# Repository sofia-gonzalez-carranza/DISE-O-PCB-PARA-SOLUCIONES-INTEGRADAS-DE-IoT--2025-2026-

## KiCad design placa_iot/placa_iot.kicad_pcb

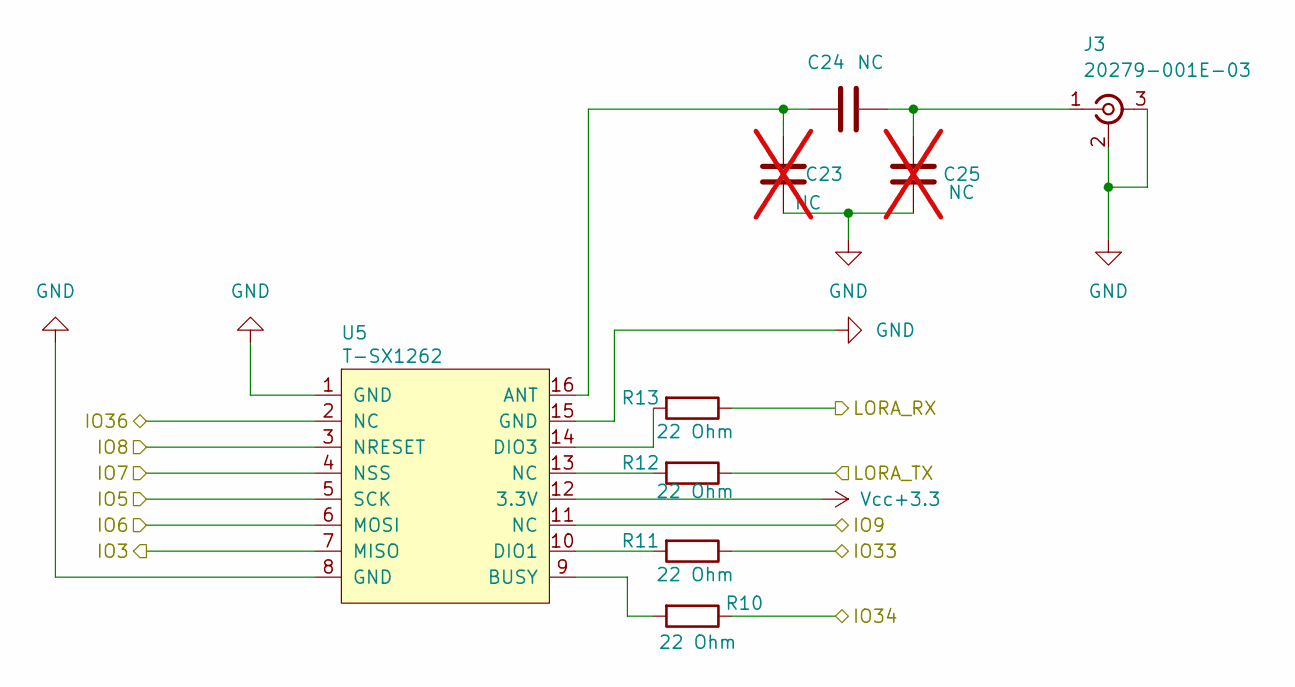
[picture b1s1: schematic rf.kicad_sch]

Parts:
C23, C25: NC; C_0402_1005Metric; not fitted
C24: NC; C_0402_1005Metric
J3: 20279-001E-03; IPEX_MHF_I
R10, R11, R12, R13: 22 Ohm; R_0402_1005Metric
U5: T-SX1262; MODULE_T_SX1262

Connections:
/MICROCONTROLADOR/IO3: U5.7 (MISO); also elsewhere on the board
/MICROCONTROLADOR/IO5: U5.5 (SCK); also elsewhere on the board
/MICROCONTROLADOR/IO6: U5.6 (MOSI); also elsewhere on the board
/MICROCONTROLADOR/IO7: U5.4 (NSS); also elsewhere on the board
/MICROCONTROLADOR/IO8: U5.3 (NRESET); also elsewhere on the board
/MICROCONTROLADOR/IO9: U5.11 (NC); also elsewhere on the board
/MICROCONTROLADOR/IO33: R11.1; also elsewhere on the board
/MICROCONTROLADOR/IO34: R10.1; also elsewhere on the board
/MICROCONTROLADOR/IO36: U5.2 (NC); also elsewhere on the board
/MICROCONTROLADOR/LORA_RX: R13.1; also elsewhere on the board
/MICROCONTROLADOR/LORA_TX: R12.1; also elsewhere on the board
GND: C23.2, C25.2, J3.2 (Ext), J3.3 (Ext), U5.1 (GND), U5.8 (GND), U5.15 (GND); also elsewhere on the board
unnamed: C24.2, C25.1, J3.1 (In)
unnamed: R12.2, U5.13 (NC)
unnamed: C23.1, C24.1, U5.16 (ANT)
unnamed: R10.2, U5.9 (BUSY)
unnamed: R11.2, U5.10 (DIO1)
unnamed: R13.2, U5.14 (DIO3)
Vcc+3.3: U5.12 (3.3V); also elsewhere on the board

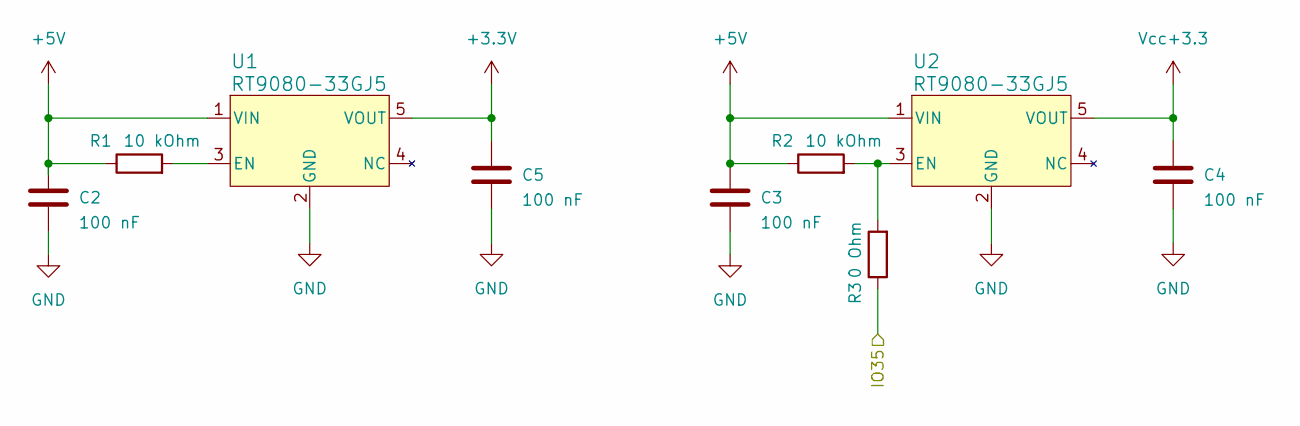
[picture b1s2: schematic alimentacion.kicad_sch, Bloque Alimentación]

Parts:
C2, C3, C4, C5: 100 nF; C_0402_1005Metric
R1, R2: 10 kOhm; R_0402_1005Metric
R3: 0 Ohm; R_0402_1005Metric
U1, U2: RT9080-33GJ5; TSOT-23-5_RIT

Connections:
+3.3V: C5.1, U1.5 (VOUT); also elsewhere on the board
+5V: C2.1, C3.1, R1.1, R2.1, U1.1 (VIN), U2.1 (VIN); also elsewhere on the board
/MICROCONTROLADOR/IO35: R3.1; also elsewhere on the board
GND: C2.2, C3.2, C4.2, C5.2, U1.2 (GND), U2.2 (GND); also elsewhere on the board
unnamed: R1.2, U1.3 (EN)
unnamed: R2.2, R3.2, U2.3 (EN)
Vcc+3.3: C4.1, U2.5 (VOUT); also elsewhere on the board

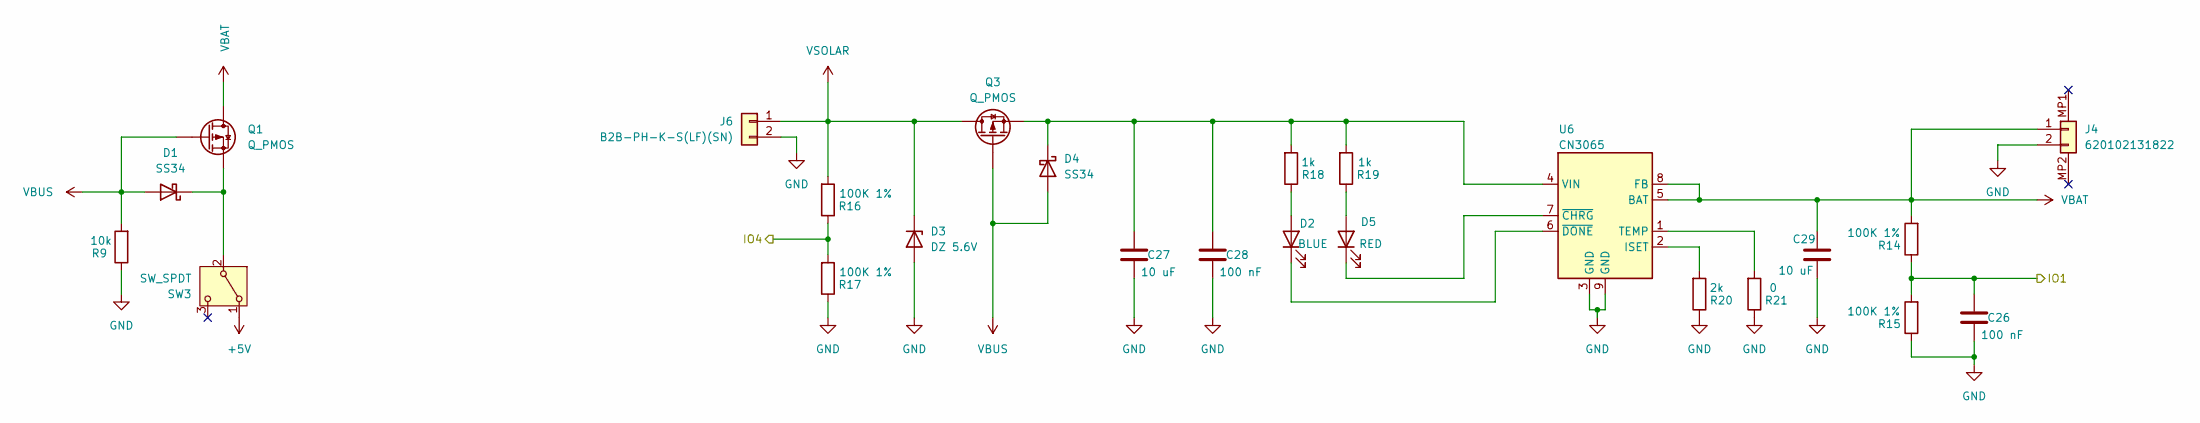
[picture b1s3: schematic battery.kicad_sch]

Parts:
C26, C28: 100 nF; C_0402_1005Metric
C27, C29: 10 uF; C_0402_1005Metric
D1, D4: SS34; D_SMA
D2: BLUE; LED_0402_1005Metric
D3: DZ 5.6V; D_SOD-123
D5: RED; LED_0402_1005Metric
J4: 620102131822; CONN_SMT_MH_SH_P2.00MM_P2
J6: B2B-PH-K-S(LF)(SN); CONN_THT_MV_JST_P2.00MM_P2
Q1, Q3: Q_PMOS; SOT-23
R9: 10k; R_0402_1005Metric
R14, R15, R16, R17: 100K 1%; R_0402_1005Metric
R18, R19: 1k; R_0402_1005Metric
R20: 2k; R_0402_1005Metric
R21: 0; R_0402_1005Metric
SW3: SW_SPDT; SW_Slide_SPDT_Angled_CK_OS102011MA1Q
U6: CN3065; DFN-8-1EP_3x3mm_P0.5mm_EP1.66x2.38mm

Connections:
+5V: SW3.1 (A); also elsewhere on the board
/MICROCONTROLADOR/IO1: C26.1, R14.1, R15.2; also elsewhere on the board
/MICROCONTROLADOR/IO4: R16.1, R17.2; also elsewhere on the board
GND: C26.2, C27.2, C28.2, C29.2, D3.2 (A), J4.2, J6.2, R9.1, R15.1, R17.1, R20.1, R21.1, U6.3 (GND), U6.9 (GND); also elsewhere on the board
unnamed: D1.1 (K), Q1.2 (S), SW3.2 (B)
unnamed: D2.2 (A), R18.1
unnamed: D2.1 (K), U6.6 (~DONE)
unnamed: C27.1, C28.1, D4.1 (K), Q3.2 (S), R18.2, R19.2, U6.4 (VIN)
unnamed: D5.2 (A), R19.1
unnamed: D5.1 (K), U6.7 (~CHRG)
unnamed: R20.2, U6.2 (ISET)
unnamed: R21.2, U6.1 (TEMP)
VBAT: C29.1, J4.1, Q1.3 (D), R14.2, U6.5 (BAT), U6.8 (FB); also elsewhere on the board
VBUS: D1.2 (A), D4.2 (A), Q1.1 (G), Q3.1 (G), R9.2; also elsewhere on the board
VSOLAR: D3.1 (K), J6.1, Q3.3 (D), R16.2

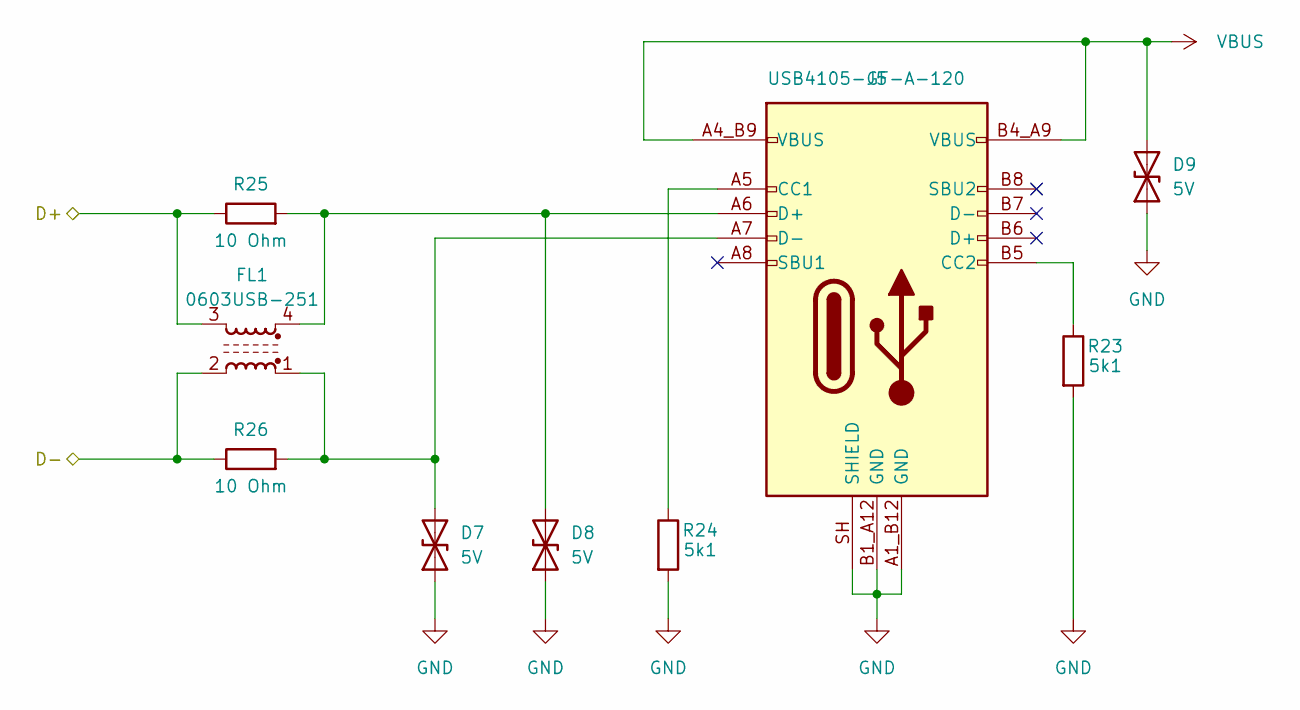
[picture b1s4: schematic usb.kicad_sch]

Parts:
D7, D8, D9: 5V; D_SOD-882
FL1: 0603USB-251; L_CommonModeChoke_Coilcraft_0603USB
J5: USB4105-GF-A-120; CONN_SMT_RH_USBC_P0.50MM_P16
R23, R24: 5k1; R_0402_1005Metric
R25, R26: 10 Ohm; R_0402_1005Metric

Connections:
/MICROCONTROLADOR/DM: FL1.3, R25.1; also elsewhere on the board
/MICROCONTROLADOR/DP: FL1.2, R26.1; also elsewhere on the board
GND: D7.1 (A1), D8.1 (A1), D9.1 (A1), J5.A1_B12 (GND), J5.B1_A12 (GND), J5.SH (SHIELD), R23.2, R24.2; also elsewhere on the board
unnamed: D7.2 (A2), FL1.1, J5.A7 (D-), R26.2
unnamed: D8.2 (A2), FL1.4, J5.A6 (D+), R25.2
unnamed: J5.A5 (CC1), R24.1
unnamed: J5.B5 (CC2), R23.1
VBUS: D9.2 (A2), J5.A4_B9 (VBUS), J5.B4_A9 (VBUS); also elsewhere on the board

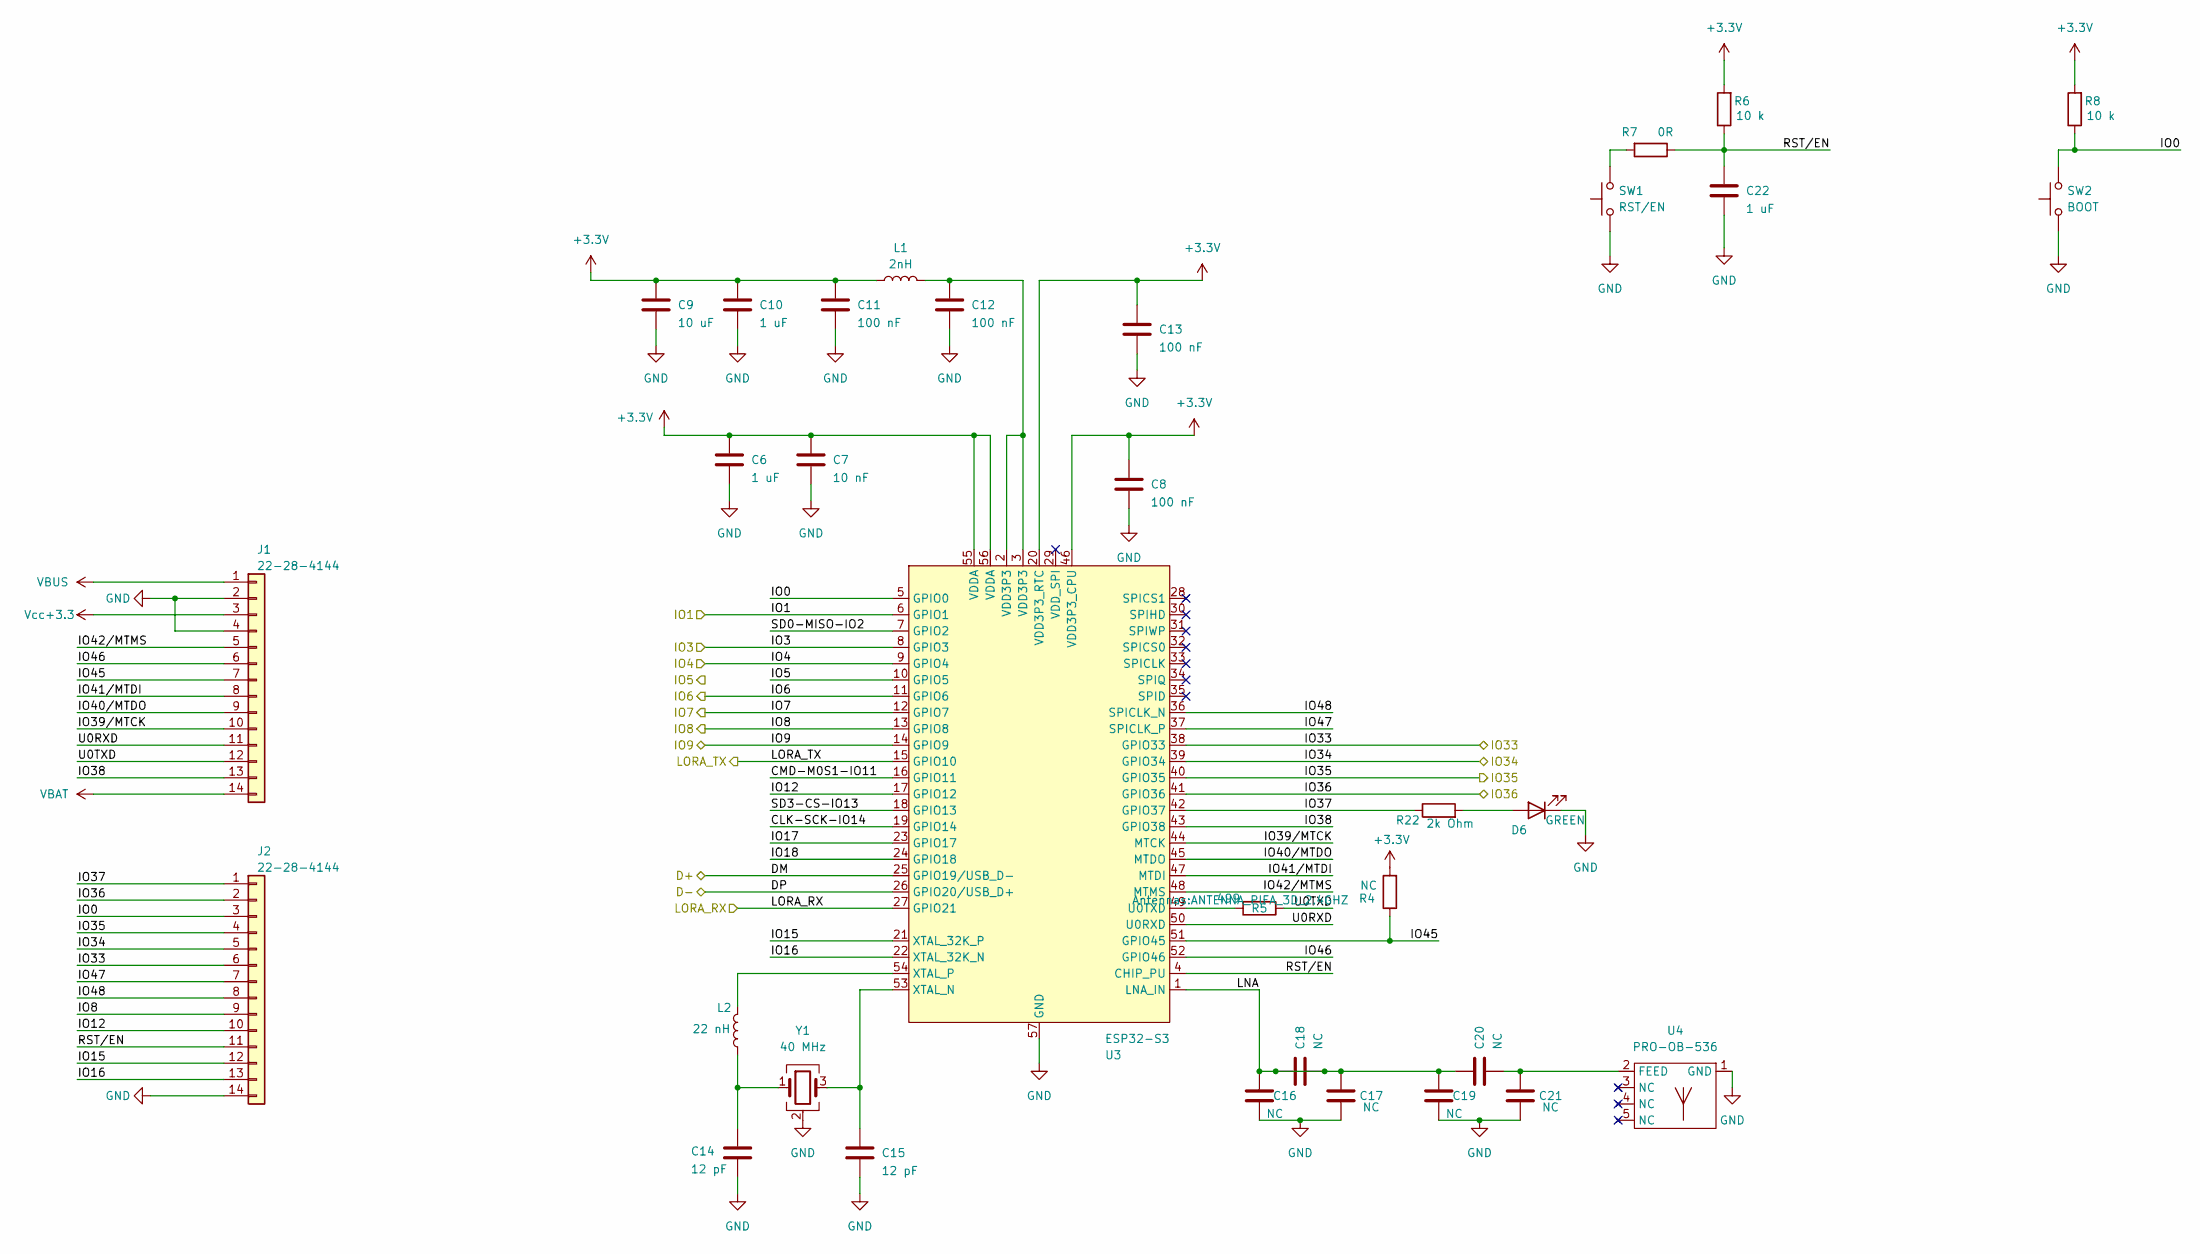
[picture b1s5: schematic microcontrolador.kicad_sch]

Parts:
C6, C10, C22: 1 uF; C_0402_1005Metric
C7: 10 nF; C_0402_1005Metric
C8, C11, C12, C13: 100 nF; C_0402_1005Metric
C9: 10 uF; C_0402_1005Metric
C14, C15: 12 pF; C_0402_1005Metric
C16, C17, C18, C19, C20, C21: NC; C_0402_1005Metric
D6: GREEN; LED_0402_1005Metric
J1, J2: 22-28-4144; CONN_THT_MV_PH_P2.54MM_P14
L1: 2nH; L_0402_1005Metric
L2: 22 nH; L_0402_1005Metric
R4: NC; R_0402_1005Metric
R5: 499; R_0402_1005Metric
R6, R8: 10 k; R_0402_1005Metric
R7: 0R; R_0402_1005Metric
R22: 2k Ohm; R_0402_1005Metric
SW1: RST/EN; SW_Push_SPST_NO_Alps_SKRK
SW2: BOOT; SW_Push_SPST_NO_Alps_SKRK
U3: ESP32-S3; QFN-56-1EP_7x7mm_P0.4mm_EP4x4mm
U4: PRO-OB-536; ANTENNA_PIFA_3D_2.4GHZ
Y1: 40 MHz; Crystal_SMD_3225-4Pin_3.2x2.5mm

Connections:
+3.3V: C6.1, C7.1, C8.1, C9.1, C10.1, C11.1, C13.1, L1.1, R4.2, R6.2, R8.2, U3.20 (VDD3P3_RTC), U3.46 (VDD3P3_CPU), U3.55 (VDDA), U3.56 (VDDA); also elsewhere on the board
/MICROCONTROLADOR/CLK-SCK-IO14: U3.19 (GPIO14)
/MICROCONTROLADOR/CMD-M0S1-IO11: U3.16 (GPIO11)
/MICROCONTROLADOR/DM: U3.25 (GPIO19/USB_D-); also elsewhere on the board
/MICROCONTROLADOR/DP: U3.26 (GPIO20/USB_D+); also elsewhere on the board
/MICROCONTROLADOR/IO0: J2.3, R8.1, SW2.2, U3.5 (GPIO0)
/MICROCONTROLADOR/IO1: U3.6 (GPIO1); also elsewhere on the board
/MICROCONTROLADOR/IO3: U3.8 (GPIO3); also elsewhere on the board
/MICROCONTROLADOR/IO4: U3.9 (GPIO4); also elsewhere on the board
/MICROCONTROLADOR/IO5: U3.10 (GPIO5); also elsewhere on the board
/MICROCONTROLADOR/IO6: U3.11 (GPIO6); also elsewhere on the board
/MICROCONTROLADOR/IO7: U3.12 (GPIO7); also elsewhere on the board
/MICROCONTROLADOR/IO8: J2.9, U3.13 (GPIO8); also elsewhere on the board
/MICROCONTROLADOR/IO9: U3.14 (GPIO9); also elsewhere on the board
/MICROCONTROLADOR/IO12: J2.10, U3.17 (GPIO12)
/MICROCONTROLADOR/IO15: J2.12, U3.21 (XTAL_32K_P)
/MICROCONTROLADOR/IO16: J2.13, U3.22 (XTAL_32K_N)
/MICROCONTROLADOR/IO17: U3.23 (GPIO17)
/MICROCONTROLADOR/IO18: U3.24 (GPIO18)
/MICROCONTROLADOR/IO33: J2.6, U3.38 (GPIO33); also elsewhere on the board
/MICROCONTROLADOR/IO34: J2.5, U3.39 (GPIO34); also elsewhere on the board
/MICROCONTROLADOR/IO35: J2.4, U3.40 (GPIO35); also elsewhere on the board
/MICROCONTROLADOR/IO36: J2.2, U3.41 (GPIO36); also elsewhere on the board
/MICROCONTROLADOR/IO37: J2.1, R22.1, U3.42 (GPIO37)
/MICROCONTROLADOR/IO38: J1.13, U3.43 (GPIO38)
/MICROCONTROLADOR/IO39/MTCK: J1.10, U3.44 (MTCK)
/MICROCONTROLADOR/IO40/MTDO: J1.9, U3.45 (MTDO)
/MICROCONTROLADOR/IO41/MTDI: J1.8, U3.47 (MTDI)
/MICROCONTROLADOR/IO42/MTMS: J1.5, U3.48 (MTMS)
/MICROCONTROLADOR/IO45: J1.7, R4.1, U3.51 (GPIO45)
/MICROCONTROLADOR/IO46: J1.6, U3.52 (GPIO46)
/MICROCONTROLADOR/IO47: J2.7, U3.37 (SPICLK_P)
/MICROCONTROLADOR/IO48: J2.8, U3.36 (SPICLK_N)
/MICROCONTROLADOR/LNA: C16.1, C17.1, C18.1, C18.2, C19.1, C20.1, U3.1 (LNA_IN)
/MICROCONTROLADOR/LORA_RX: U3.27 (GPIO21); also elsewhere on the board
/MICROCONTROLADOR/LORA_TX: U3.15 (GPIO10); also elsewhere on the board
/MICROCONTROLADOR/RST/EN: C22.1, J2.11, R6.1, R7.1, U3.4 (CHIP_PU)
/MICROCONTROLADOR/SD0-MISO-IO2: U3.7 (GPIO2)
/MICROCONTROLADOR/SD3-CS-IO13: U3.18 (GPIO13)
/MICROCONTROLADOR/U0RXD: J1.11, U3.50 (U0RXD)
/MICROCONTROLADOR/U0TXD: J1.12, R5.1
GND: C6.2, C7.2, C8.2, C9.2, C10.2, C11.2, C12.2, C13.2, C14.2, C15.2, C16.2, C17.2, C19.2, C21.2, C22.2, D6.1 (K), J1.2, J1.4, J2.14, SW1.1, SW2.1, U3.57 (GND), U4.1 (GND), Y1.2 (G), Y1.4 (G); also elsewhere on the board
unnamed: C12.1, L1.2, U3.2 (VDD3P3), U3.3 (VDD3P3)
unnamed: C14.1, L2.1, Y1.1
unnamed: D6.2 (A), R22.2
unnamed: R7.2, SW1.2
unnamed: R5.2, U3.49 (U0TXD)
unnamed: C15.1, U3.53 (XTAL_N), Y1.3
unnamed: L2.2, U3.54 (XTAL_P)
unnamed: C20.2, C21.1, U4.2 (FEED)
VBAT: J1.14; also elsewhere on the board
VBUS: J1.1; also elsewhere on the board
Vcc+3.3: J1.3; also elsewhere on the board

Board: 4 copper layers, 88 parts (2 on the bottom side), 69 nets, no tracks yet.

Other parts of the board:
M1, M2, M3, M4: MountingHole_2.5mm_Pad

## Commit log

2026-05-18 Library added
2026-05-18 Project Created
2026-05-19 Tarea_1_Resistencia
2026-05-19 Librería Creada
2026-05-19 Esquemáticos creados
2026-05-19 Alimetación creada
2026-05-19 Microcontrolador en proceso
2026-05-20 Bloque microcontrolador terminado
2026-05-20 RF completado
2026-05-20 Batería completa
2026-05-20 Esquemático USB completado
2026-05-20 Esquemático acabado
2026-05-20 Layout iniciado y resolución de errores de huellas
2026-05-21 Colocación de elementos
2026-05-22 Layout Completado
